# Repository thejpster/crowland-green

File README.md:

# Crowland Green

These are some design files for the Northants and Cambs N Gauge Society layout, "Crowland Green"

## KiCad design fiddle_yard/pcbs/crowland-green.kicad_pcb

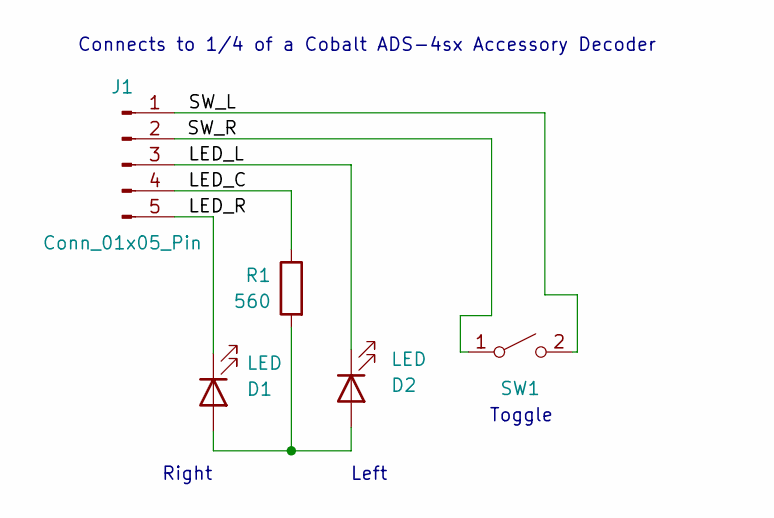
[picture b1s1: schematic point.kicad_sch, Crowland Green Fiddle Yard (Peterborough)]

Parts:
D1, D2: LED; LED_0805_2012Metric; JLCPCB C84256
J1: Conn_01x05_Pin; PinHeader_1x05_P2.54mm_Horizontal
R1: 560; R_0805_2012Metric; JLCPCB C28636
SW1: SW_SPST; SW_Push_1P1T_XKB_TS-1187A; JLCPCB C318884

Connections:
/Point1/LED_C: J1.4, R1.1
/Point1/LED_L: D2.1 (K), J1.3
/Point1/LED_R: D1.1 (K), J1.5
/Point1/SW_L: J1.1, SW1.2 (B)
/Point1/SW_R: J1.2, SW1.1 (A)
unnamed: D1.2 (A), D2.2 (A), R1.2

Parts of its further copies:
D3, D4, D5, D6, D7, D8, D9, D10, D11, D12, D13, D14: LED; LED_0805_2012Metric; JLCPCB C84256
J2, J3, J4, J5, J6, J7: Conn_01x05_Pin; PinHeader_1x05_P2.54mm_Horizontal
R2, R3, R4, R5, R6, R7: 560; R_0805_2012Metric; JLCPCB C28636
SW2, SW3, SW4, SW5, SW6, SW7: SW_SPST; SW_Push_1P1T_XKB_TS-1187A; JLCPCB C318884

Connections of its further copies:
/Point2/LED_C: J2.4, R2.1
/Point2/LED_L: D4.1 (K), J2.3
/Point2/LED_R: D3.1 (K), J2.5
/Point2/SW_L: J2.1, SW2.2 (B)
/Point2/SW_R: J2.2, SW2.1 (A)
/Point3/LED_C: J3.4, R3.1
/Point3/LED_L: D6.1 (K), J3.3
/Point3/LED_R: D5.1 (K), J3.5
/Point3/SW_L: J3.1, SW3.2 (B)
/Point3/SW_R: J3.2, SW3.1 (A)
/Point4/LED_C: J4.4, R4.1
/Point4/LED_L: D8.1 (K), J4.3
/Point4/LED_R: D7.1 (K), J4.5
/Point4/SW_L: J4.1, SW4.2 (B)
/Point4/SW_R: J4.2, SW4.1 (A)
/Point5/LED_C: J5.4, R5.1
/Point5/LED_L: D10.1 (K), J5.3
/Point5/LED_R: D9.1 (K), J5.5
/Point5/SW_L: J5.1, SW5.2 (B)
/Point5/SW_R: J5.2, SW5.1 (A)
/Point6/LED_C: J6.4, R6.1
/Point6/LED_L: D12.1 (K), J6.3
/Point6/LED_R: D11.1 (K), J6.5
/Point6/SW_L: J6.1, SW6.2 (B)
/Point6/SW_R: J6.2, SW6.1 (A)
/Point7/LED_C: J7.4, R7.1
/Point7/LED_L: D14.1 (K), J7.3
/Point7/LED_R: D13.1 (K), J7.5
/Point7/SW_L: J7.1, SW7.2 (B)
/Point7/SW_R: J7.2, SW7.1 (A)
unnamed: D3.2 (A), D4.2 (A), R2.2
unnamed: D5.2 (A), D6.2 (A), R3.2
unnamed: D7.2 (A), D8.2 (A), R4.2
unnamed: D9.2 (A), D10.2 (A), R5.2
unnamed: D11.2 (A), D12.2 (A), R6.2
unnamed: D13.2 (A), D14.2 (A), R7.2

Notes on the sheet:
Right
Connects to 1/4 of a Cobalt ADS-4sx Accessory Decoder
Left
Toggle

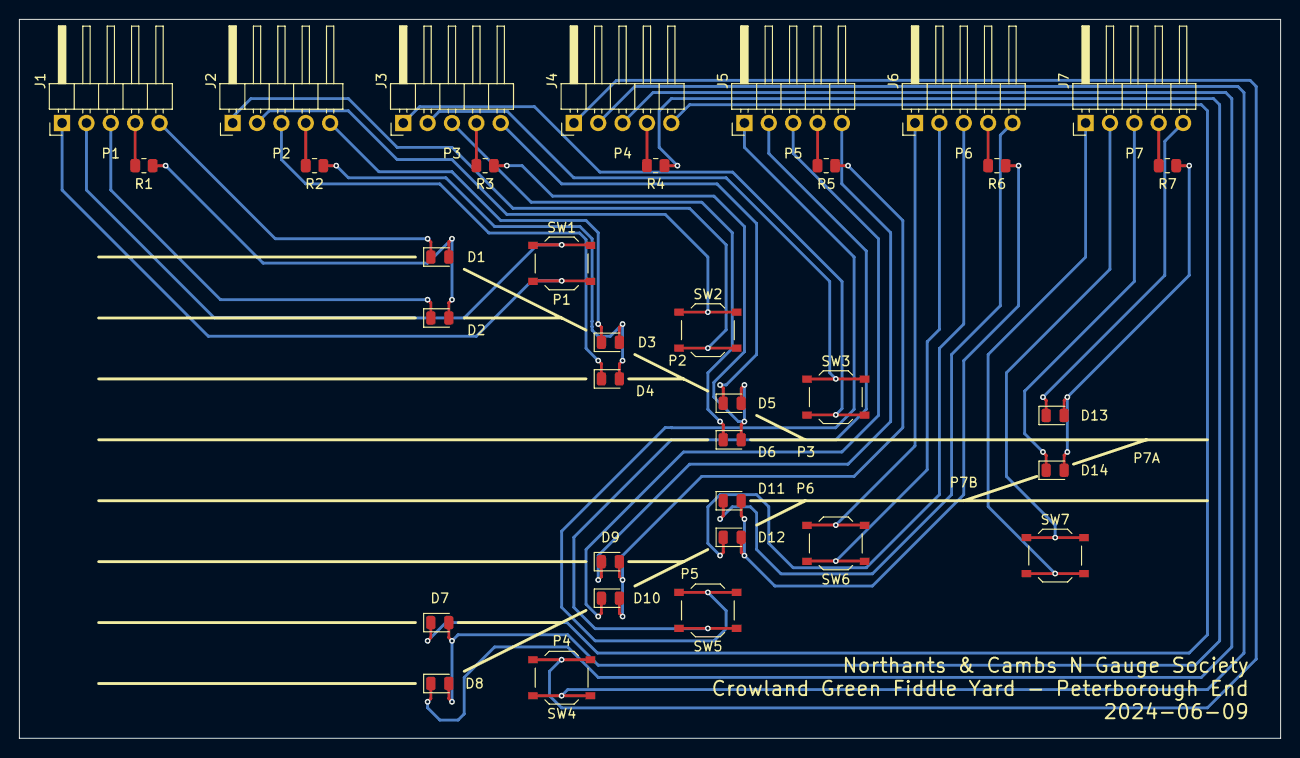
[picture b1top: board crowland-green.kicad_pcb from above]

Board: 2 copper layers, 131.4 x 74.9 mm, 35 parts (0 on the bottom side), 42 nets.

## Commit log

2024-06-09 As ordered from JLCPCB today.
    I had to manually modify the POS file to suit JLCPCB requirements, but in
    the end I went for bare boards instead of PCBAs.
